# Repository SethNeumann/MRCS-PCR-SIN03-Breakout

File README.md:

# REPO NAME:     MRCS-PCR-SIN03-Breakout

## License: Creative Commons Attribution-NonCommercial-ShareAlike

This board is to provide a neater and more reliable mounting for the PCR-SIN03 ringing generators often found on eBay,
the board has a barrel jack so the module can be powered by a wall wart, a voltage divider to provide 5V for the INHibit line
to gate ringing or create a cadence. There is also an 8 position 0.100 connector for power, daisy chain, INH/5VR and ringing output.

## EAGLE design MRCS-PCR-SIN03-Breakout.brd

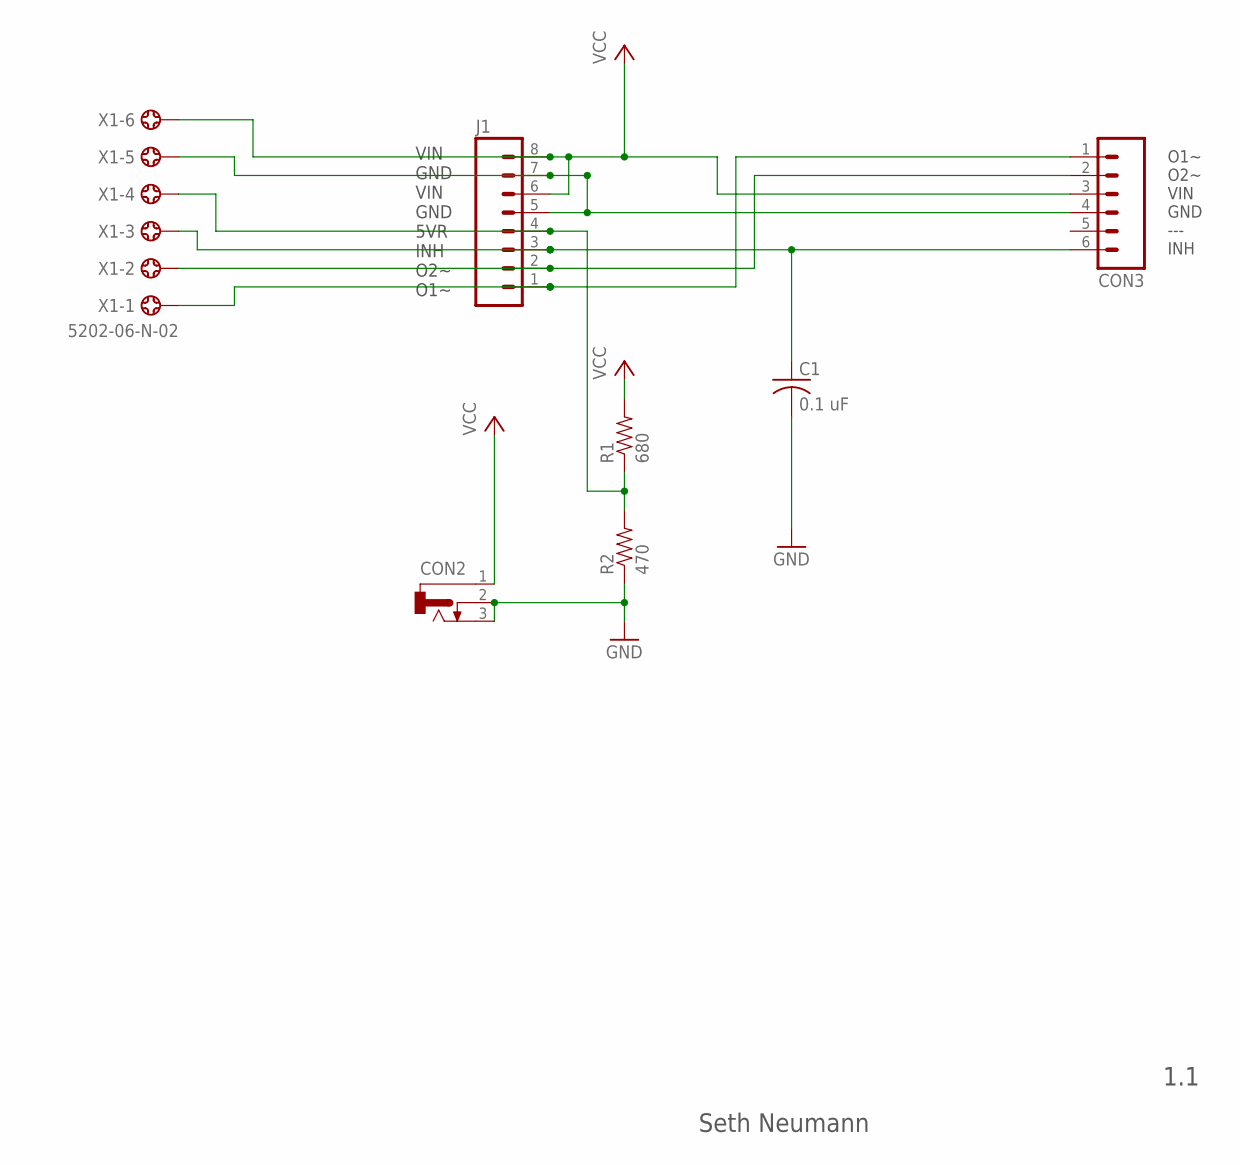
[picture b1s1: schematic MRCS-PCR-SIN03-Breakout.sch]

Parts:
C1: 0.1 uF; C-PTH-0.100
CON2: CONNECTOR-DC-POWER-RA; DCJ0202
CON3: CONNECTOR-M06POLAR; MOLEX-1X6
J1: CONNECTOR-M08LOCK; 1X08_LOCK
R1: 680; AXIAL-0.4-RES
R2: 470; AXIAL-0.4-RES
X1: 5202-06-N-02

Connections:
5VR: J1.4, R1.P$1 (1), R2.P$2 (2), X1.4
GND: C1.2, CON2.2, CON2.3, CON3.4, J1.5, J1.7, R2.P$1 (1), X1.5
INH: C1.1, CON3.6, J1.3, X1.3
O1: CON3.1, J1.1, X1.1
O2: CON3.2, J1.2, X1.2
VCC: CON2.1, CON3.3, J1.6, J1.8, R1.P$2 (2), X1.6

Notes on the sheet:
Seth Neumann
1.1
VIN GND VIN GND 5VR INH O2~ O1~
O1~ O2~ VIN GND --- INH

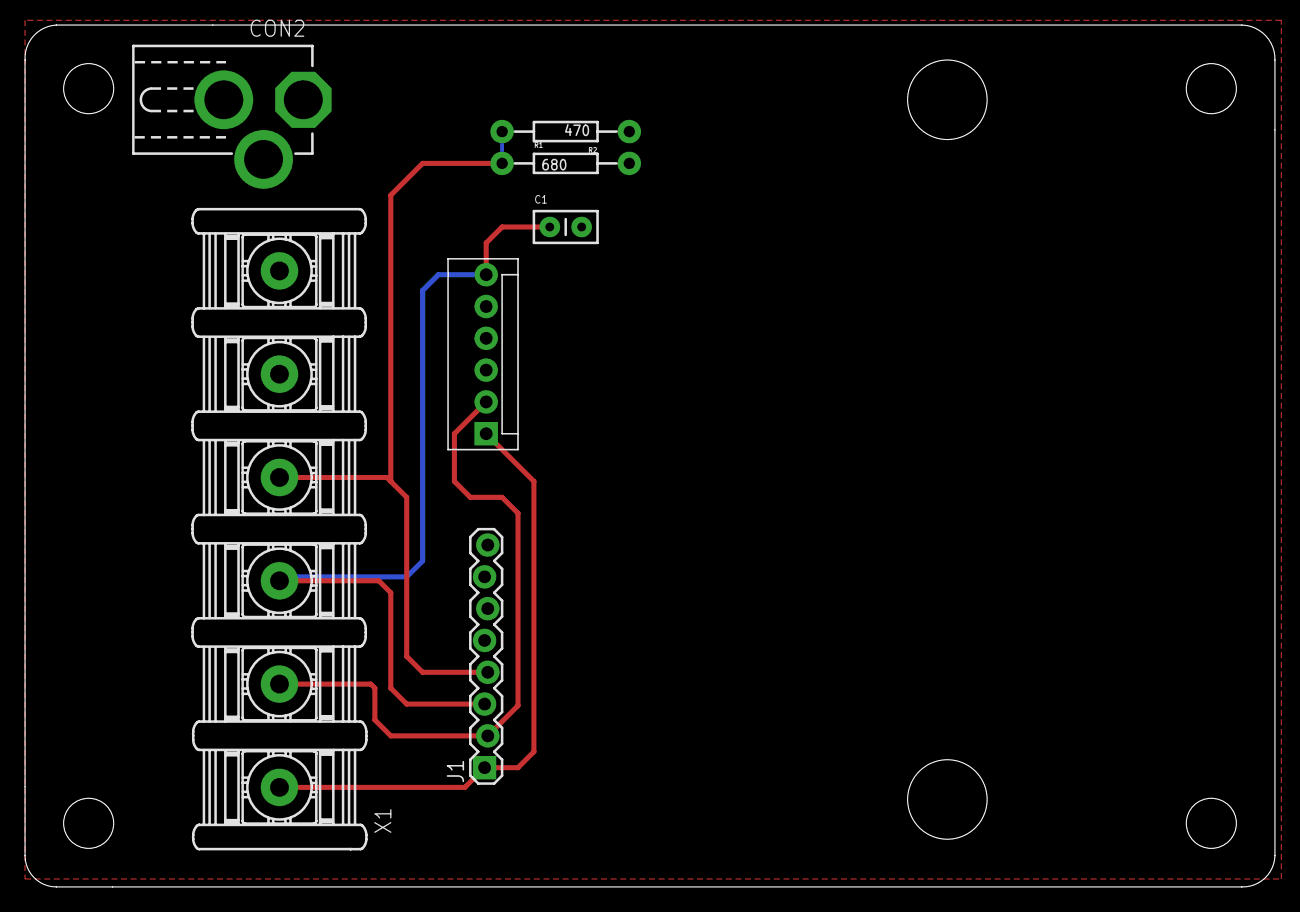
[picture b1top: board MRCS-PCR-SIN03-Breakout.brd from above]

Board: 2 copper layers, 99.8 x 68.8 mm, 11 parts (0 on the bottom side), 6 nets.

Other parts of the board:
U$1: BOARD-DINRAIL-2.7IN
U$2: MRCSLOGOTOP
U$3: CA-PROP65WARNING
U$4: MRCSLOGOBTM

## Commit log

2023-09-22 initialcommit
2023-09-22 moved work files into Github
    creating new repository
2023-09-25 first fab
2023-10-07 changes for 1st board run
2023-10-07 Added 8 mm screw barrier block
    this might be more useful for the phone folks as it supports spade lugs. Plenty of room on the board!
